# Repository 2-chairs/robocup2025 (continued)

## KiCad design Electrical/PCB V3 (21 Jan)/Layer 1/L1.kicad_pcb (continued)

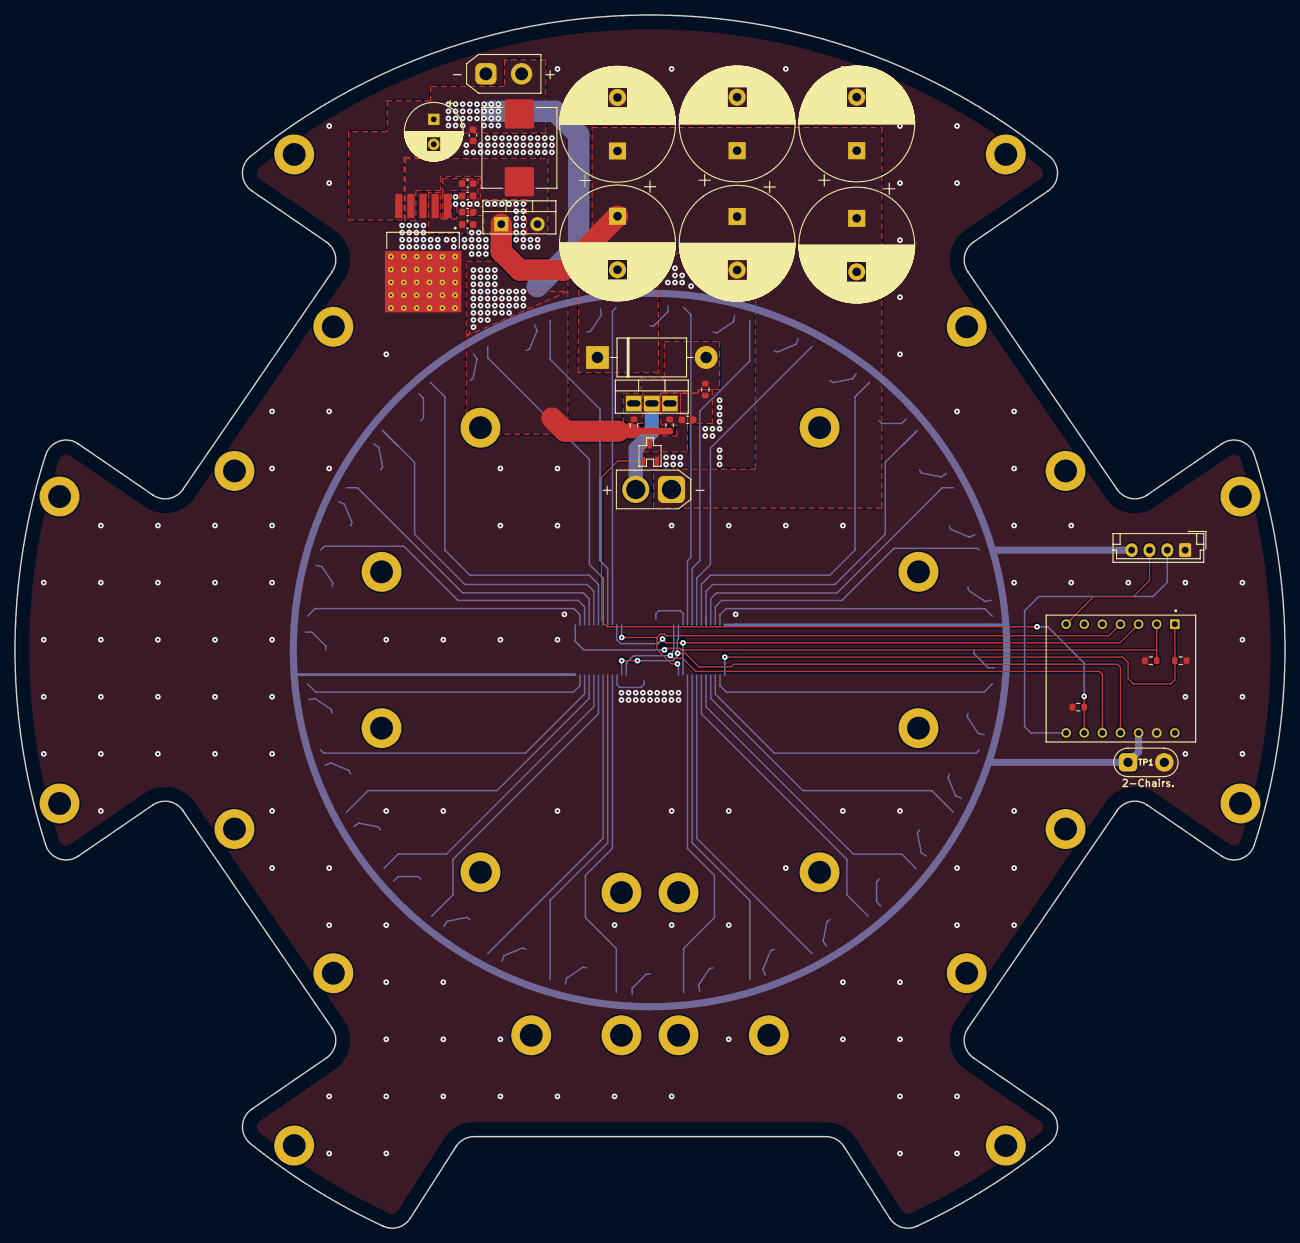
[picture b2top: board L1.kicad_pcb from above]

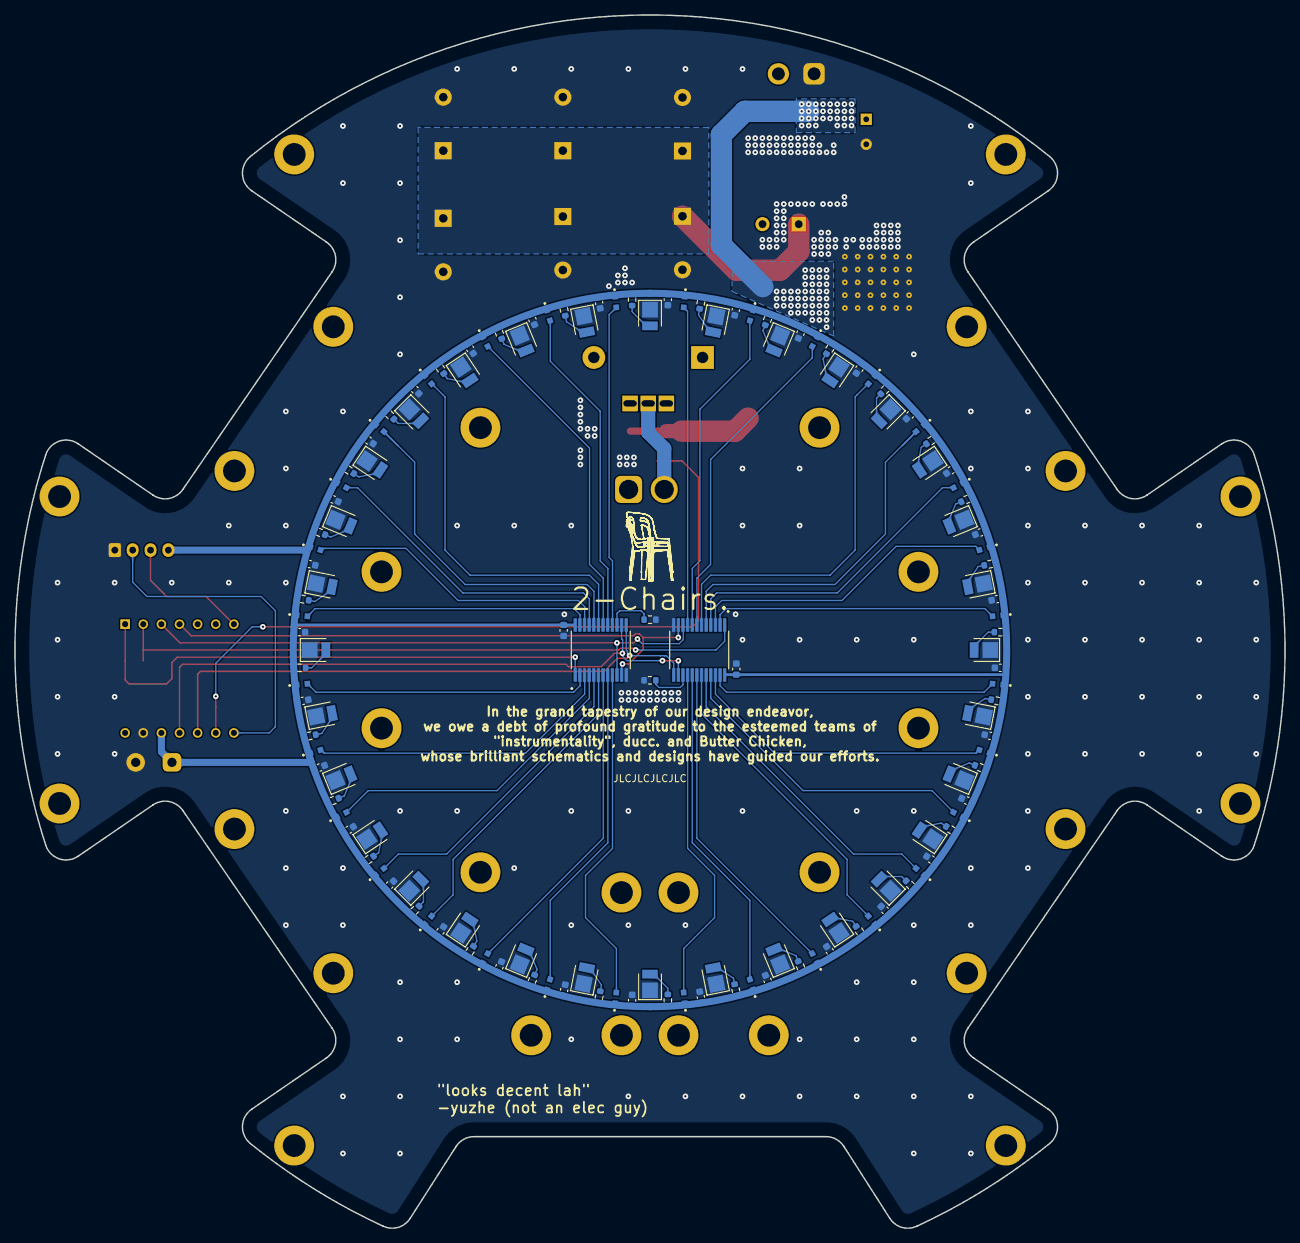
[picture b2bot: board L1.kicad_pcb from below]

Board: 2 copper layers, 178.0 x 170.0 mm, 194 parts (134 on the bottom side), 87 nets.

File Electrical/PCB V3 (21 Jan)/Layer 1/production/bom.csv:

Designator,Footprint,Quantity,Value,LCSC Part #
"C1, C10, C11, C12, C13, C14, C15, C16, C17, C18, C19, C2, C20, C21, C22, C23, C24, C25, C26, C27, C28, C29, C3, C30, C31, C32, C4, C5, C6, C7, C8, C9",0603,32,1uF,
"C33, C34",0603,2,.1uF,
C35,0603,1,0.1uF,C3011705
C36,CP_Radial_D8.0mm_P3.50mm,1,100uF,C249586
"C37, C38, C39, C41, C42, C43",CP_Radial_D16.0mm_P7.50mm,6,1000uF,C249586
C40,0603,1,0.68uF,C59782
C44,0603,1,1500pF,C107060
D1,D_DO-201AD_P15.24mm_Horizontal,1,1N5401,C179506
D2,TO-220-2_Vertical,1,MBR745,
J1,JST_EH_B4B-EH-A_1x04_P2.50mm_Vertical,1,Conn_01x04,
J2,AMASS_XT30UPB-M_1x02_P5.0mm_Vertical,1,Conn_01x02,
L33,L_APV_APH1040,1,33uH,C2875750
"LED1, LED10, LED11, LED12, LED13, LED14, LED15, LED16, LED17, LED18, LED19, LED2, LED20, LED21, LED22, LED23, LED24, LED25, LED26, LED27, LED28, LED29, LED3, LED30, LED31, LED32, LED4, LED5, LED6, LED7, LED8, LED9",LED_PLCC_2835,32,WHITE 3528,
"LED_1, LED_10, LED_11, LED_12, LED_13, LED_14, LED_15, LED_16, LED_17, LED_18, LED_19, LED_2, LED_20, LED_21, LED_22, LED_23, LED_24, LED_25, LED_26, LED_27, LED_28, LED_29, LED_3, LED_30, LED_31, LED_32, LED_4, LED_5, LED_6, LED_7, LED_8, LED_9",XDCR_ALS-PT19-315C_L177_TR8,32,R_Photo,
Q2,TO-220-3_Vertical,1,STP75NF75,C13678
Q4,SOT95P237X112-3N,1,IRLML6344TRPBF,
"R1, R10, R11, R12, R13, R14, R15, R16, R17, R18, R19, R2, R20, R21, R22, R23, R24, R25, R26, R27, R28, R29, R3, R30, R31, R32, R4, R5, R6, R7, R8, R9",0603,32,0R39,
"R33, R34",0603,2,3k24,
R35,0603,1,36.9K/56k,C23082
R36,0603,1,2K/2.94k,C22843
"R37, R43",0603,2,10k,
R38,0603,1,3K,C137748
R39,0603,1,10K,C25804
R40,0603,1,470R,C21190
R41,0603,1,1K,C21190
R42,0603,1,20R,C22950
TP1,testpoint_2pad_2-chairs.,1,Led 3v3 & Gnd TP,
U1,VREG_TPS79625KTTR,1,LM2587S-ADJ,
"U2, U3",SOP65P780X200-24N,2,CD74HC4067SM,
U4,AMASS_XT30U-M_1x02_P5.0mm_Vertical,1,XT30UPB-M,
U5,XiaoSeeedStudioEsp32,1,113991054,

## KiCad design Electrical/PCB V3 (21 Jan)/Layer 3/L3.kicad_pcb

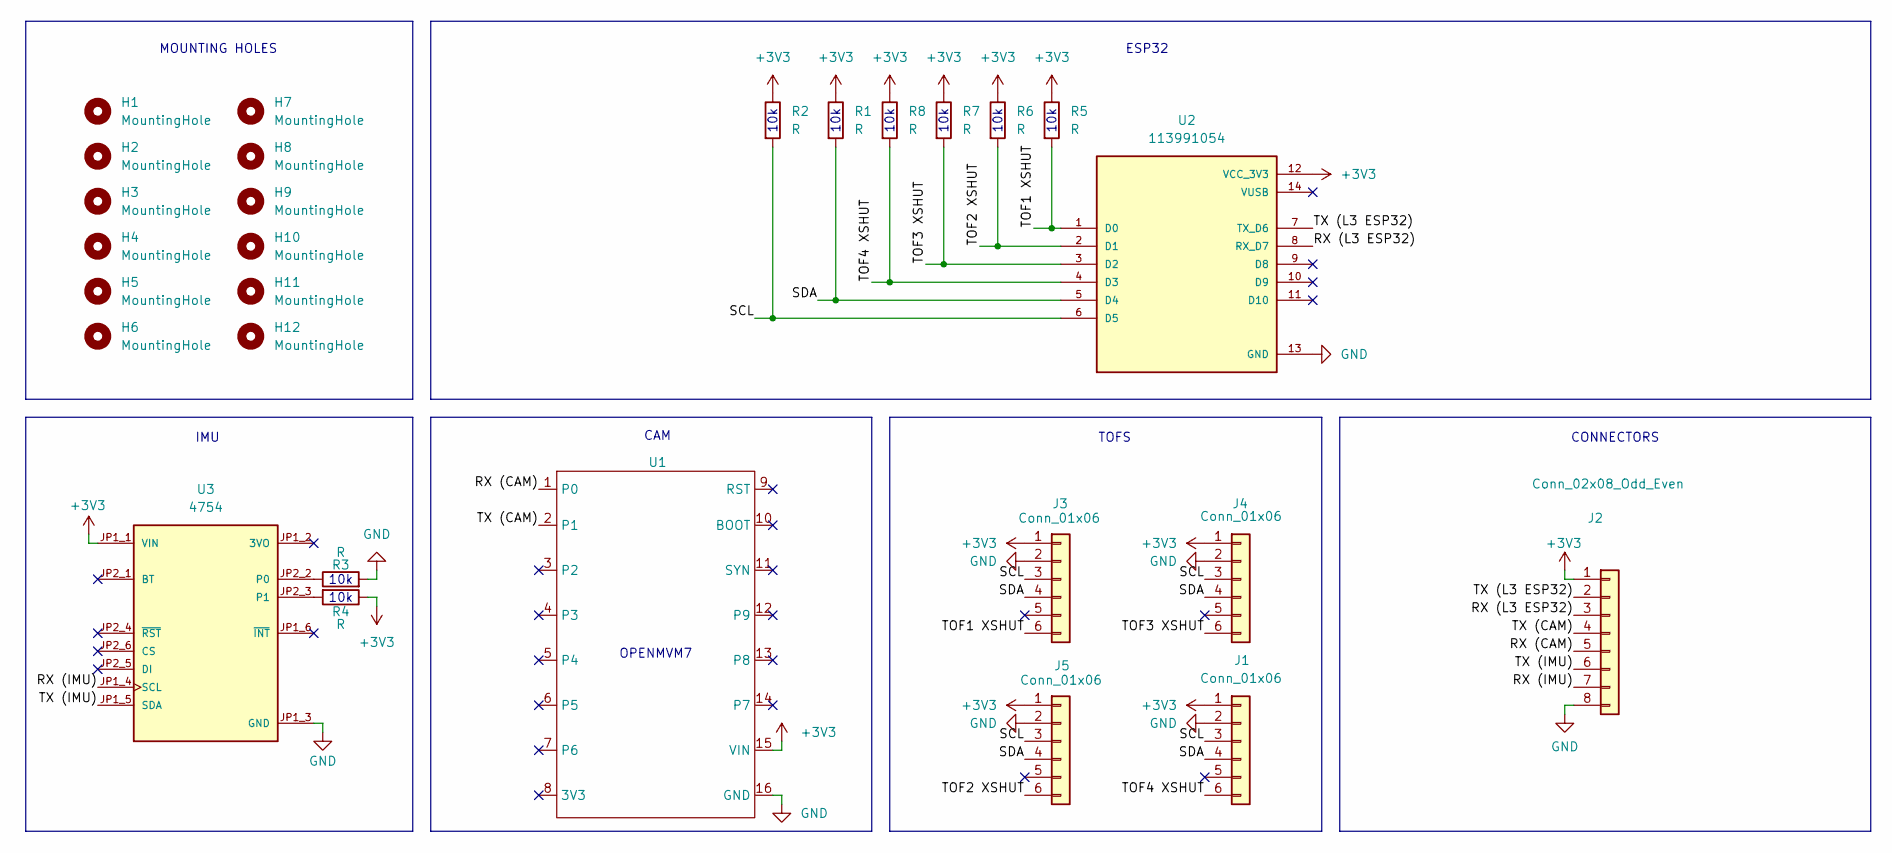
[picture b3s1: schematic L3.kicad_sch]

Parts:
H1, H2, H3, H4, H5, H6, H7, H8, H9, H10, H11, H12: MountingHole; MountingHole_3.2mm_M3_Pad_Via
J1, J3, J4, J5: Conn_01x06; PinHeader_1x06_P2.54mm_Vertical
J2: Conn_02x08_Odd_Even; JST_XH_B8B-XH-A_1x08_P2.50mm_Vertical
R1, R2, R3, R4, R5, R6, R7, R8: R; R_0603_1608Metric_Pad0.98x0.95mm_HandSolder
U1: OPENMV_M7
U2: 113991054; MODULE_113991054; PARTREV 23/05/2022
U3: 4754; MODULE_4754; PARTREV 2021-03-16

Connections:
+3V3: J1.1, J2.1, J3.1, J4.1, J5.1, R1.1, R2.1, R4.1, R5.1, R6.1, R7.1, R8.1, U1.15 (VIN), U2.12 (VCC_3V3), U3.JP1_1 (VIN)
/RX (CAM): J2.5, U1.1 (P0)
/RX (IMU): J2.7, U3.JP1_4 (SCL)
/RX (L3 ESP32): J2.3, U2.8 (RX_D7)
/SCL: J1.3, J3.3, J4.3, J5.3, R2.2, U2.6 (D5)
/SDA: J1.4, J3.4, J4.4, J5.4, R1.2, U2.5 (D4)
/TOF1 XSHUT: J3.6, R5.2, U2.1 (D0)
/TOF2 XSHUT: J5.6, R6.2, U2.2 (D1)
/TOF3 XSHUT: J4.6, R7.2, U2.3 (D2)
/TOF4 XSHUT: J1.6, R8.2, U2.4 (D3)
/TX (CAM): J2.4, U1.2 (P1)
/TX (IMU): J2.6, U3.JP1_5 (SDA)
/TX (L3 ESP32): J2.2, U2.7 (TX_D6)
GND: J1.2, J2.8, J3.2, J4.2, J5.2, R3.2, U1.16 (GND), U2.13 (GND), U3.JP1_3 (GND)
unnamed: R3.1, U3.JP2_2 (P0)
unnamed: R4.2, U3.JP2_3 (P1)

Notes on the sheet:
IMU
10k
TOFS
ESP32
CONNECTORS
MOUNTING HOLES
CAM
OPENMVM7

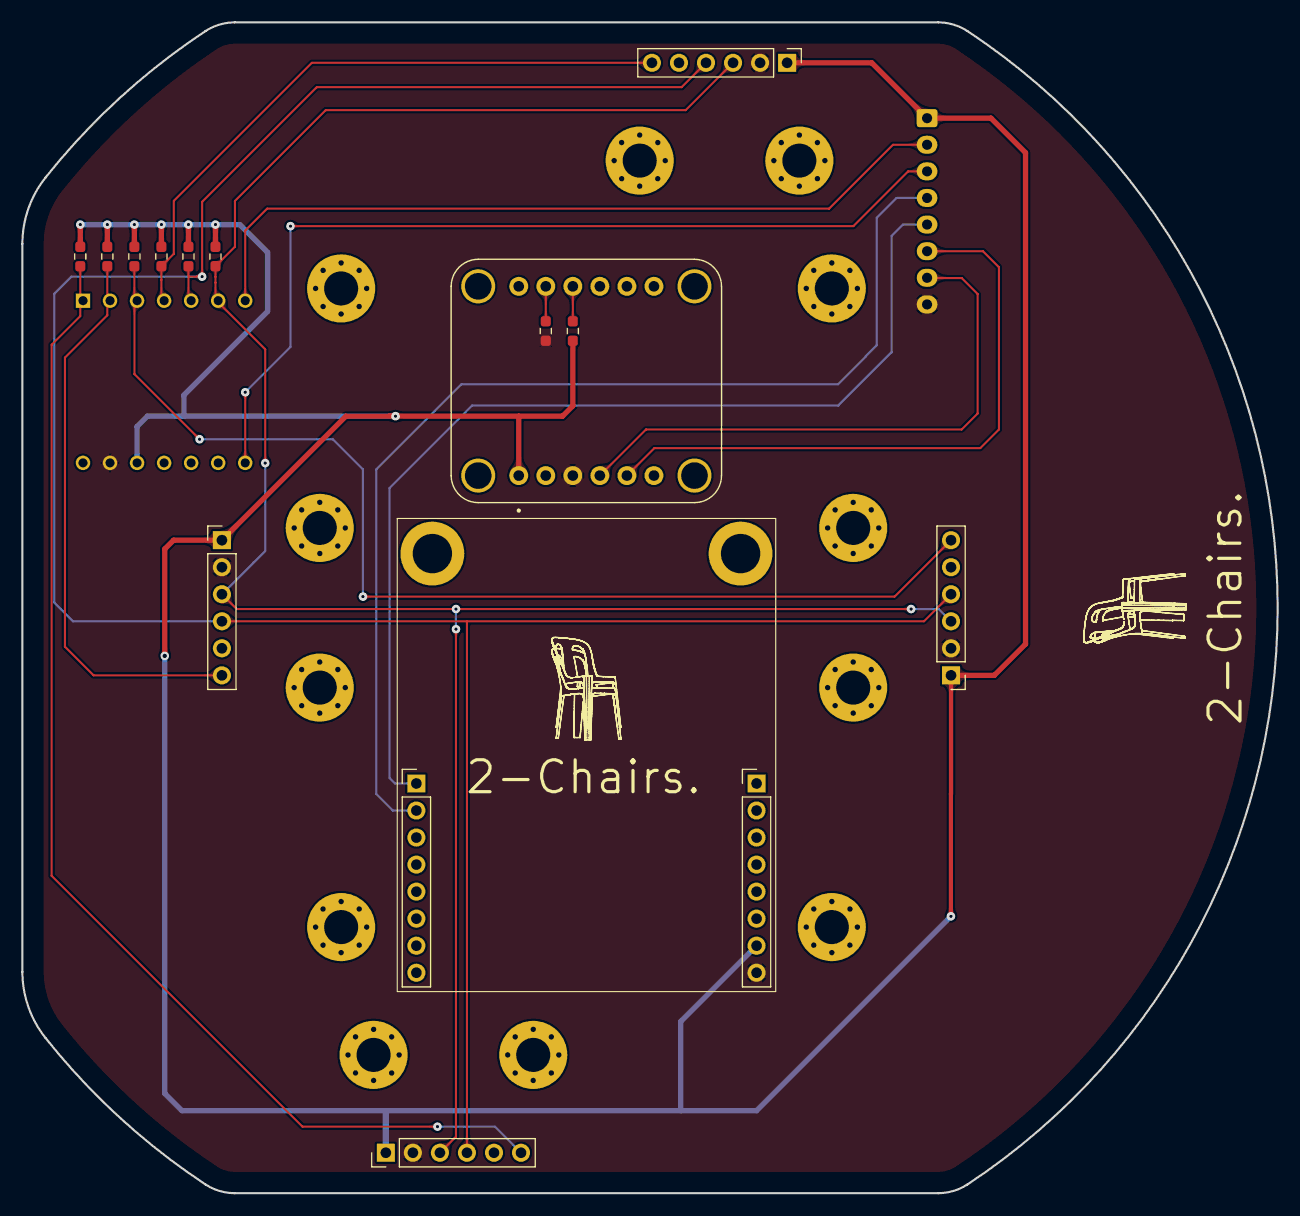
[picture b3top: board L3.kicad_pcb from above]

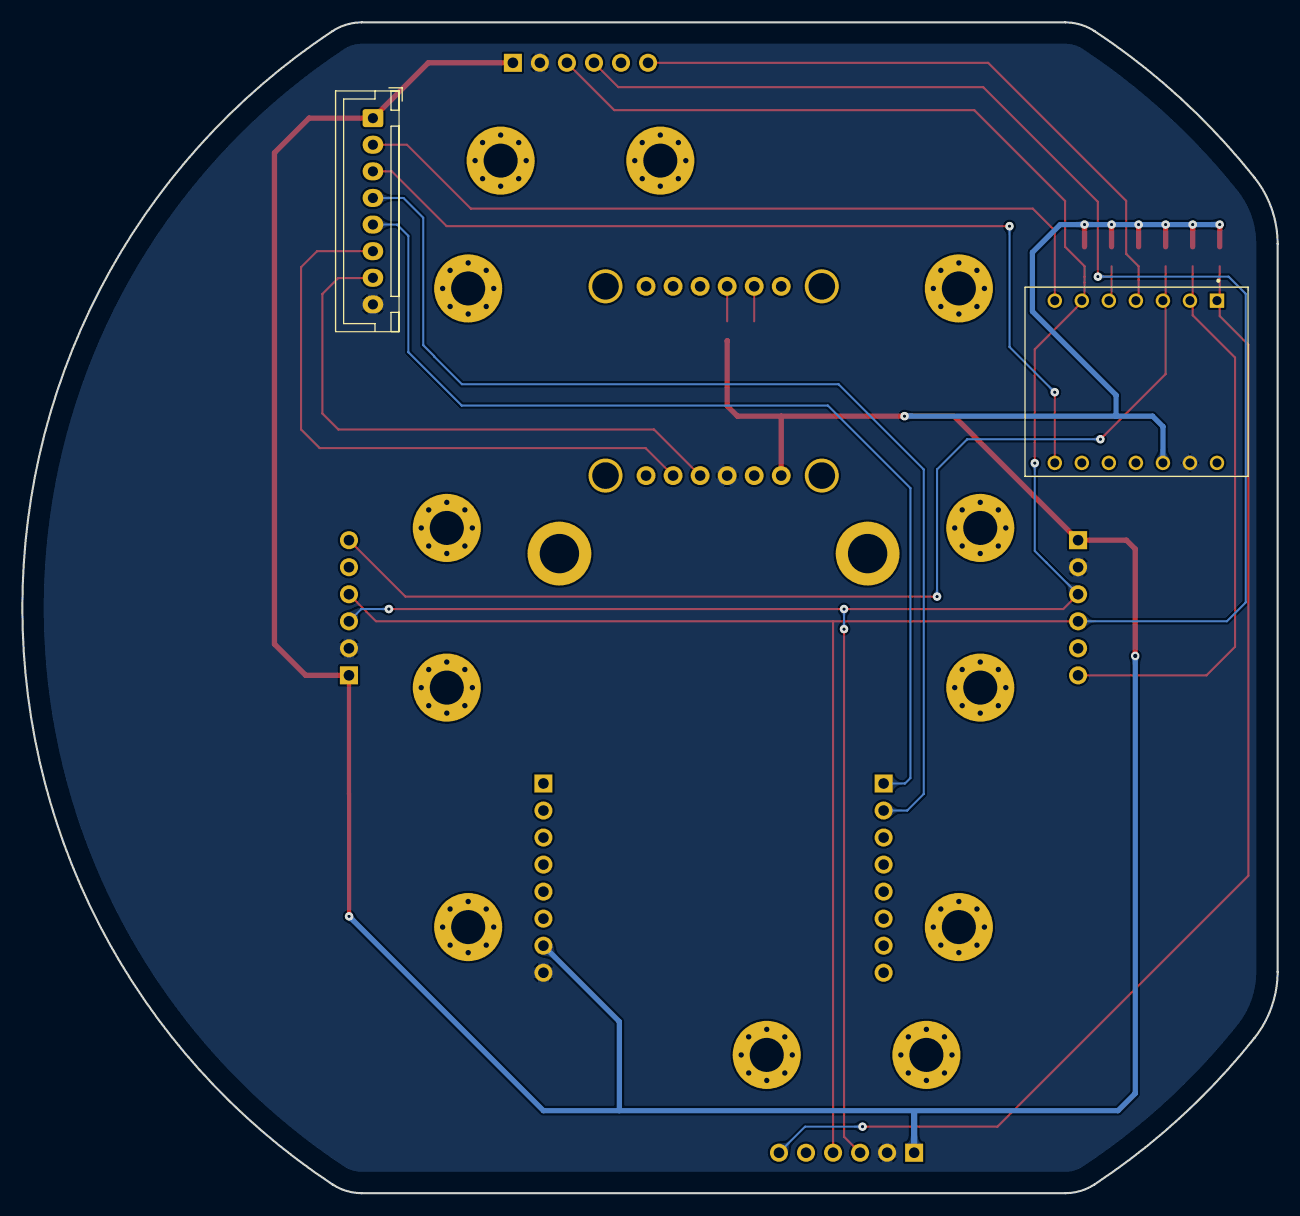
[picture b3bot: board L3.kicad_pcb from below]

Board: 2 copper layers, 117.9 x 110.0 mm, 28 parts (2 on the bottom side), 16 nets.

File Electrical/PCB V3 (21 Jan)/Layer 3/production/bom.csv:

Designator,Footprint,Quantity,Value,LCSC Part #
"J1, J3, J4, J5",PinHeader_1x06_P2.54mm_Vertical,4,Conn_01x06,
J2,JST_XH_B8B-XH-A_1x08_P2.50mm_Vertical,1,Conn_02x08_Odd_Even,
"R1, R2, R3, R4, R5, R6, R7, R8",0603,8,R,
U1,OPENMV_M7,1,~,
U2,MODULE_113991054,1,113991054,
U3,MODULE_4754,1,4754,

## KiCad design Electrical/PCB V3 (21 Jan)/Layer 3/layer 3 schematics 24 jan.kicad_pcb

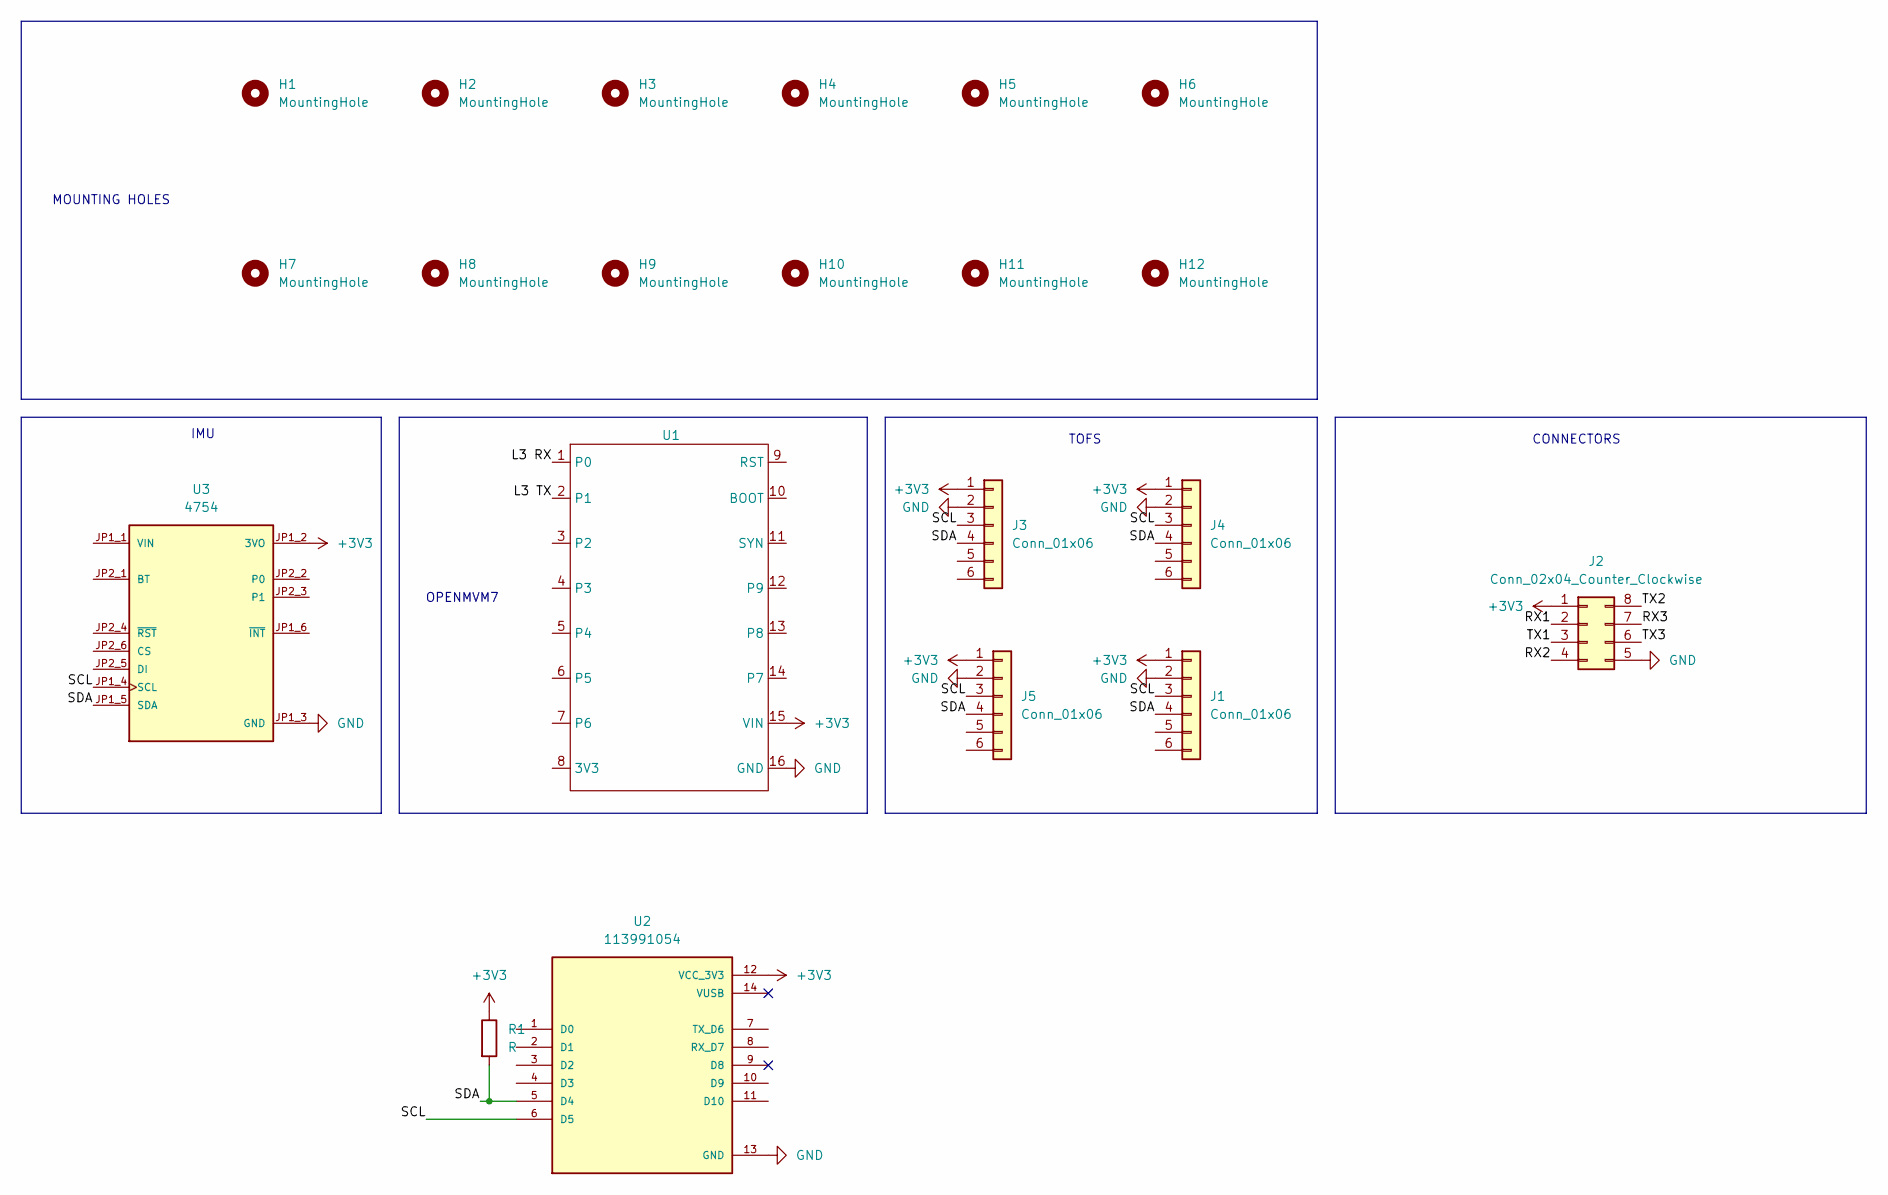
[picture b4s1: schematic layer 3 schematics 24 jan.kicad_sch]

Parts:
H1, H2, H3, H4, H5, H6, H7, H8, H9, H10, H11, H12: MountingHole; MountingHole_3.2mm_M3_Pad_Via
J1, J3, J4, J5: Conn_01x06; PinHeader_1x06_P2.54mm_Vertical
J2: Conn_02x04_Counter_Clockwise; JST_PHD_B8B-PHDSS_2x04_P2.00mm_Vertical
R1: R
U1: OPENMV_M7
U2: 113991054; XiaoSeeedStudioEsp32; PARTREV 23/05/2022
U3: 4754; MODULE_4754; PARTREV 2021-03-16

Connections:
+3V3: J1.1, J2.1, J3.1, J4.1, J5.1, R1.1, U1.15 (VIN), U2.12 (VCC_3V3), U3.JP1_2 (3VO)
/L3 RX: U1.1 (P0)
/L3 TX: U1.2 (P1)
/RX1: J2.2
/RX2: J2.4
/RX3: J2.7
/SCL: J1.3, J3.3, J4.3, J5.3, U2.6 (D5), U3.JP1_4 (SCL)
/SDA: J1.4, J3.4, J4.4, J5.4, R1.2, U2.5 (D4), U3.JP1_5 (SDA)
/TX1: J2.3
/TX2: J2.8
/TX3: J2.6
GND: J1.2, J2.5, J3.2, J4.2, J5.2, U1.16 (GND), U2.13 (GND), U3.JP1_3 (GND)

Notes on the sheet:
IMU
TOFS
CONNECTORS
MOUNTING HOLES
OPENMVM7

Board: 2 copper layers, 19 parts (0 on the bottom side), 4 nets, no tracks yet.

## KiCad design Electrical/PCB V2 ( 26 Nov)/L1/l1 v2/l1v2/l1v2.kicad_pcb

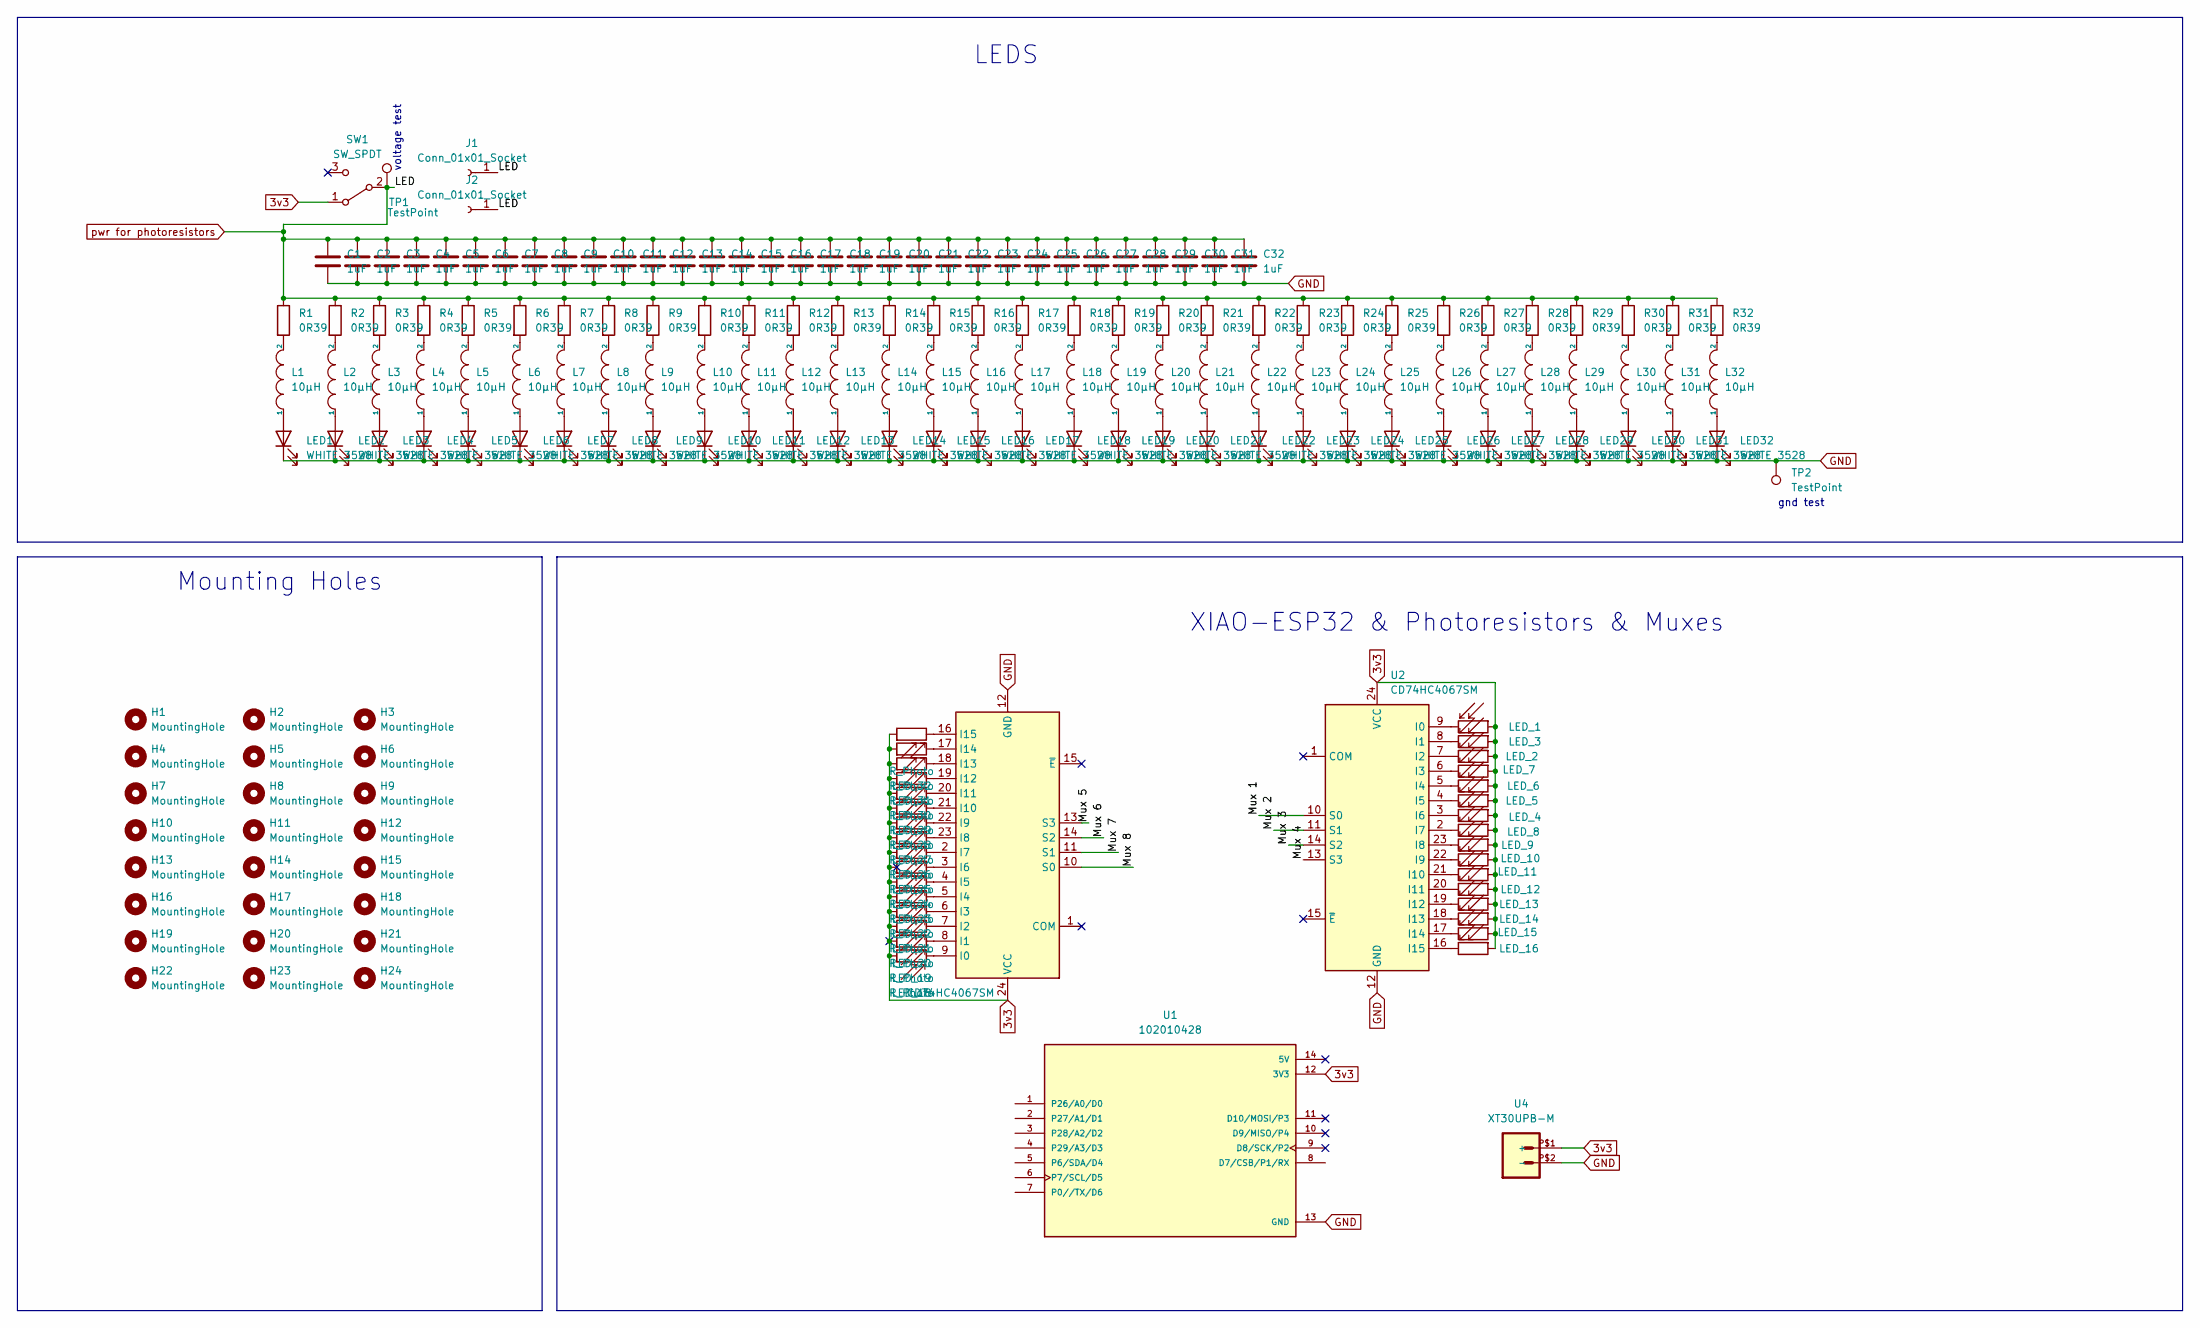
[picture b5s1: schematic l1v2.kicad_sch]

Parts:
C1, C2, C3, C4, C5, C6, C7, C8, C9, C10, C11, C12, C13, C14, C15, C16, C17, C18, C19, C20, C21, C22, C23, C24, C25, C26, C27, C28, C29, C30, C31, C32: 1uF; C_0603_1608Metric
H1, H2, H3, H4, H5, H6, H7, H8, H9, H10, H11, H12, H13, H14, H15, H16, H17, H18, H19, H20, H21, H22, H23, H24: MountingHole; MountingHole_3.2mm_M3_DIN965_Pad
J1: Conn_01x01_Socket; SolderWirePad_1x01_SMD_1x2mm
J2: Conn_01x01_Socket; SolderWire-0.5sqmm_1x01_D0.9mm_OD2.1mm
L1, L2, L3, L4, L5, L6, L7, L8, L9, L10, L11, L12, L13, L14, L15, L16, L17, L18, L19, L20, L21, L22, L23, L24, L25, L26, L27, L28, L29, L30, L31, L32: 10µH; L_0805_2012Metric
LED1, LED2, LED3, LED4, LED5, LED6, LED7, LED8, LED9, LED10, LED11, LED12, LED13, LED14, LED15, LED16, LED17, LED18, LED19, LED20, LED21, LED22, LED23, LED24, LED25, LED26, LED27, LED28, LED29, LED30, LED31, LED32: WHITE 3528; LED_PLCC_2835
LED_1, LED_2, LED_3, LED_4, LED_5, LED_6, LED_7, LED_8, LED_9, LED_10, LED_11, LED_12, LED_13, LED_14, LED_15, LED_16, LED_17, LED_18, LED_19, LED_20, LED_21, LED_22, LED_23, LED_24, LED_25, LED_26, LED_27, LED_28, LED_29, LED_30, LED_31, LED_32: R_Photo; XDCR_ALS-PT19-315C_L177_TR8
R1, R2, R3, R4, R5, R6, R7, R8, R9, R10, R11, R12, R13, R14, R15, R16, R17, R18, R19, R20, R21, R22, R23, R24, R25, R26, R27, R28, R29, R30, R31, R32: 0R39; R_0603_1608Metric
SW1: SW_SPDT; Nidec_Copal_CAS-120A
TP1, TP2: TestPoint; TestPoint_2Pads_Pitch2.54mm_Drill0.8mm
U1: 102010428; MCU_Seeed_ESP32C3; PARTREV 1.3
U2, U3: CD74HC4067SM; SOP65P780X200-24N
U4: XT30UPB-M

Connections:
3v3: LED_1.1, LED_2.1, LED_3.1, LED_4.1, LED_5.1, LED_6.1, LED_7.1, LED_8.1, LED_9.1, LED_10.1, LED_11.1, LED_12.1, LED_13.1, LED_14.1, LED_15.1, LED_16.1, LED_17.1, LED_18.1, LED_19.1, LED_20.1, LED_21.1, LED_22.1, LED_23.1, LED_24.1, LED_25.1, LED_26.1, LED_27.1, LED_28.1, LED_29.1, LED_30.1, LED_31.1, LED_32.1, SW1.1 (A), U1.12 (3V3), U2.24 (VCC), U3.24 (VCC), U4.P$1 (+)
/Mux Com (1-16): U1.1 (P26/A0/D0), U2.15 (~E)
/Mux Com (17-32): U1.2 (P27/A1/D1), U3.1 (COM)
/SCL: U1.6 (P7/SCL/D5); also elsewhere on the board
/SDA: U1.5 (P6/SDA/D4); also elsewhere on the board
GND: C1.2, C2.2, C3.2, C4.2, C5.2, C6.2, C7.2, C8.2, C9.2, C10.2, C11.2, C12.2, C13.2, C14.2, C15.2, C16.2, C17.2, C18.2, C19.2, C20.2, C21.2, C22.2, C23.2, C24.2, C25.2, C26.2, C27.2, C28.2, C29.2, C30.2, C31.2, C32.2, LED1.1 (K), LED2.1 (K), LED3.1 (K), LED4.1 (K), LED5.1 (K), LED6.1 (K), LED7.1 (K), LED8.1 (K), LED9.1 (K), LED10.1 (K), LED11.1 (K), LED12.1 (K), LED13.1 (K), LED14.1 (K), LED15.1 (K), LED16.1 (K), LED17.1 (K), LED18.1 (K), LED19.1 (K), LED20.1 (K), LED21.1 (K), LED22.1 (K), LED23.1 (K), LED24.1 (K), LED25.1 (K), LED26.1 (K), LED27.1 (K), LED28.1 (K), LED29.1 (K), LED30.1 (K), LED31.1 (K), LED32.1 (K), TP2.1, U1.13 (GND), U2.12 (GND), U3.12 (GND), U4.P$2 (-)
unnamed: L1.2, R1.2
unnamed: L2.2, R2.2
unnamed: L3.2, R3.2
unnamed: L4.2, R4.2
unnamed: L5.2, R5.2
unnamed: L6.2, R6.2
unnamed: L7.2, R7.2
unnamed: L8.2, R8.2
unnamed: L9.2, R9.2
unnamed: L10.2, R10.2
unnamed: L11.2, R11.2
unnamed: L12.2, R12.2
unnamed: L13.2, R13.2
unnamed: L14.2, R14.2
unnamed: L15.2, R15.2
unnamed: L16.2, R16.2
unnamed: L17.2, R17.2
unnamed: L18.2, R18.2
unnamed: L19.2, R19.2
unnamed: L20.2, R20.2
unnamed: L21.2, R21.2
unnamed: L22.2, R22.2
unnamed: L23.2, R23.2
unnamed: L24.2, R24.2
unnamed: L25.2, R25.2
unnamed: L26.2, R26.2
unnamed: L27.2, R27.2
unnamed: L28.2, R28.2
unnamed: L29.2, R29.2
unnamed: L30.2, R30.2
unnamed: L31.2, R31.2
unnamed: L32.2, R32.2
unnamed: L1.1, LED1.2 (A)
unnamed: L2.1, LED2.2 (A)
unnamed: L3.1, LED3.2 (A)
unnamed: L4.1, LED4.2 (A)
unnamed: L5.1, LED5.2 (A)
unnamed: L6.1, LED6.2 (A)
unnamed: L7.1, LED7.2 (A)
unnamed: L8.1, LED8.2 (A)
unnamed: L9.1, LED9.2 (A)
unnamed: L10.1, LED10.2 (A)
unnamed: L11.1, LED11.2 (A)
unnamed: L12.1, LED12.2 (A)
unnamed: L13.1, LED13.2 (A)
unnamed: L14.1, LED14.2 (A)
unnamed: L15.1, LED15.2 (A)
unnamed: L16.1, LED16.2 (A)
unnamed: L17.1, LED17.2 (A)
unnamed: L18.1, LED18.2 (A)
unnamed: L19.1, LED19.2 (A)
unnamed: L20.1, LED20.2 (A)
unnamed: L21.1, LED21.2 (A)
unnamed: L22.1, LED22.2 (A)
unnamed: L23.1, LED23.2 (A)
unnamed: L24.1, LED24.2 (A)
unnamed: L25.1, LED25.2 (A)
unnamed: L26.1, LED26.2 (A)
unnamed: L27.1, LED27.2 (A)
unnamed: L28.1, LED28.2 (A)
unnamed: L29.1, LED29.2 (A)
unnamed: L30.1, LED30.2 (A)
unnamed: L31.1, LED31.2 (A)
unnamed: L32.1, LED32.2 (A)
unnamed: LED_1.2, U2.9 (I0)
unnamed: LED_3.2, U2.8 (I1)
unnamed: LED_2.2, U2.7 (I2)
unnamed: LED_7.2, U2.6 (I3)
unnamed: LED_6.2, U2.5 (I4)
unnamed: LED_5.2, U2.4 (I5)
unnamed: LED_4.2, U2.3 (I6)
unnamed: LED_8.2, U2.2 (I7)
unnamed: LED_9.2, U2.23 (I8)
unnamed: LED_10.2, U2.22 (I9)
unnamed: LED_11.2, U2.21 (I10)
unnamed: LED_12.2, U2.20 (I11)
unnamed: LED_13.2, U2.19 (I12)
unnamed: LED_14.2, U2.18 (I13)
unnamed: LED_15.2, U2.17 (I14)
unnamed: LED_16.2, U2.16 (I15)
unnamed: LED_17.2, U3.9 (I0)
unnamed: LED_18.2, U3.8 (I1)
unnamed: LED_19.2, U3.7 (I2)
unnamed: LED_20.2, U3.6 (I3)
unnamed: LED_21.2, U3.5 (I4)
unnamed: LED_22.2, U3.4 (I5)
unnamed: LED_23.2, U3.3 (I6)
unnamed: LED_24.2, U3.2 (I7)
unnamed: LED_25.2, U3.23 (I8)
unnamed: LED_26.2, U3.22 (I9)
unnamed: LED_27.2, U3.21 (I10)
unnamed: LED_28.2, U3.20 (I11)
unnamed: LED_29.2, U3.19 (I12)
unnamed: LED_30.2, U3.18 (I13)
unnamed: LED_31.2, U3.17 (I14)
unnamed: LED_32.2, U3.16 (I15)
pwr for photoresistors: C1.1, C2.1, C3.1, C4.1, C5.1, C6.1, C7.1, C8.1, C9.1, C10.1, C11.1, C12.1, C13.1, C14.1, C15.1, C16.1, C17.1, C18.1, C19.1, C20.1, C21.1, C22.1, C23.1, C24.1, C25.1, C26.1, C27.1, C28.1, C29.1, C30.1, C31.1, C32.1, J1.1, J2.1, R1.1, R2.1, R3.1, R4.1, R5.1, R6.1, R7.1, R8.1, R9.1, R10.1, R11.1, R12.1, R13.1, R14.1, R15.1, R16.1, R17.1, R18.1, R19.1, R20.1, R21.1, R22.1, R23.1, R24.1, R25.1, R26.1, R27.1, R28.1, R29.1, R30.1, R31.1, R32.1, SW1.2 (B), TP1.1

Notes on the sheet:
Mounting Holes
LEDS
gnd test
XIAO-ESP32 & Photoresistors & Muxes
voltage test

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
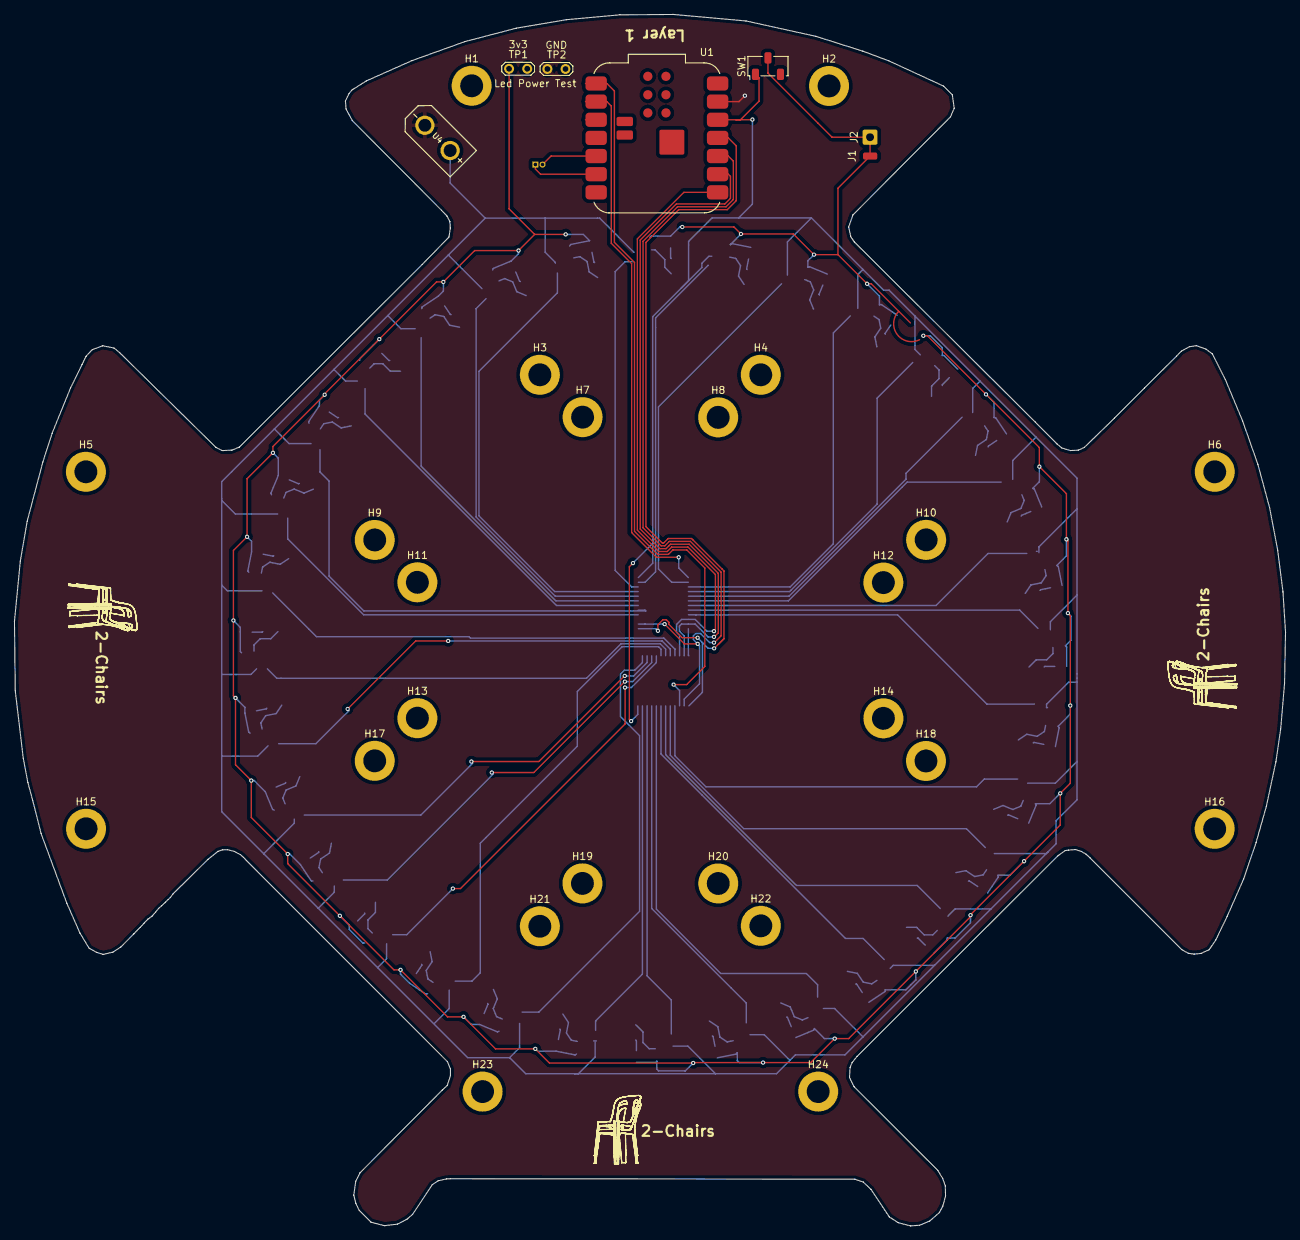
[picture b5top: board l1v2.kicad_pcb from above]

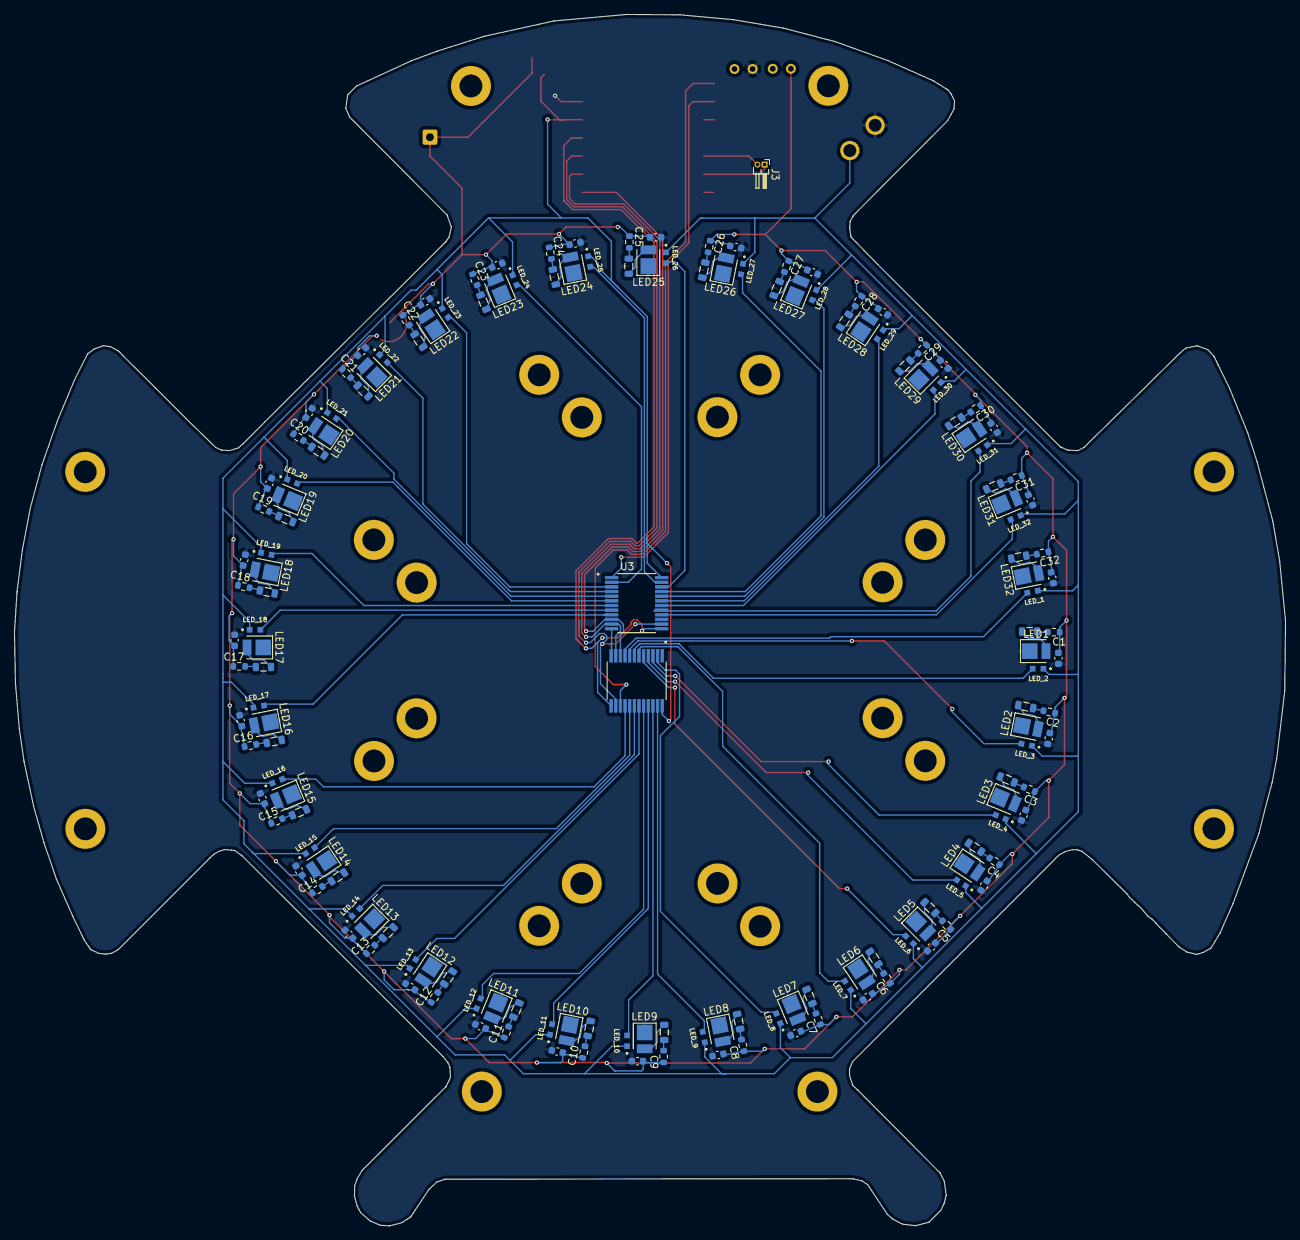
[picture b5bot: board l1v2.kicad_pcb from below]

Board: 2 copper layers, 177.9 x 169.6 mm, 194 parts (163 on the bottom side), 107 nets.

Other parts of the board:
J3: Conn_01x02; PinHeader_1x02_P1.00mm_Horizontal

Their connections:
/SCL: J3.1; also elsewhere on the board
/SDA: J3.2; also elsewhere on the board
